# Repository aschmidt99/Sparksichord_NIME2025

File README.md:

# Sparksichord_NIME2025
 A repo for schematics, CAD, and audiovisual examples to accompany the NIME 2025 Sparksichord conference paper by Adam Schmidt, Jeffrey Snyder, Gian Torrano Jacobs, Joseph Gascho, Joyce Chen, and Andrew McPherson.

 Primary contact: a.schmidt24@imperial.ac.uk

The Sparksichord is a practical implementation of a 4-octave/48-channel Lorentz Force feedback sustainer system using brass strings, permanent magnets, optical sensors, and custom analog electronics. The Sparksichord is an augmentation of a 1970’s Zuckermann ‘Z-Box’ Harpsichord and uses its own keyboard to control the volume of each string’s feedback/actuation. Here we provide a basic overview of the working principles of the Sparksichord. For a more comprehensive guide to Lorentz Force actuation, please see _The Sparksichord: Practical Implementation of a Lorentz Force Electromagnetic Actuation and Feedback System_.

## Audiovisual example:

# Lorentz Force
The cumulative force felt by a charged particle exposed to electric and magnetic fields is known as the _Lorentz Force_. A special case of the Lorentz Force (sometimes referred to as the _Laplace Force_) describes the magnetic force felt by a current-carrying wire exposed to a magnetic field:

$$
\begin{align}
 \mathbf{F} = I \mathbf{L} \times \mathbf{B}
\end{align}
$$

where $\mathbf{F}$ is the force vector felt by the wire, $I$ is the current through the wire, $\mathbf{B}$ is the magnetic field vector, and $\mathbf{L}$ is the length of the wire exposed to the magnetic field.

Inputing an audio signal to the string such as white noise, you should hear the string vibrate most prominently at its natural resonant frequencies. It is possible to drive a string with an oscillator tuned to match the string’s fundamental frequency, but doing so can be tricky. Depending on the material properties of the actuated string, some of the actuation current may be dissipated as heat in the string’s internal resistance, introducing thermal expansion of the string and causing it to lengthen and reduce its tension. This brings the frequency of the string down causing it to no longer match the frequency of the open-loop actuation signal.

## Heat Buildup \& String Detuning

The resistivity of some conductive metals are displayed in the figure below. Metals such as yellow and red brass are much less resistive than iron and steel, meaning they are more robust to string detuning, though it should be noted that heat treatment or work-hardening of the string material is also a factor, where annealed metal will typically have higher conductivity than a heat-treated metal. Heat-treating or other processes that increase the stength of a metal string are often required for strings to withstand the tensions typically found in musical instruments, so it is fair to assume any wire intended for stringing instruments will have slightly greater resistivity than in the figure below.

The intensity of detuning is proportional to its heat buildup and therefore proportional to the resistivity inherent to the string:

$$
\begin{align}
  Q = I^2Rt
\end{align}
$$

where $Q$ = heat buildup, $I$ = electric current, $R$ = resistance, and $t$ = time. Though this formula suggests that the string may heat up and continue to detune indefinitely as electric current is applied, there is an element of heat dissipation into the surrounding air and any other materials the string is in contact with.  In other words, for a real system, the detuning effect from heat buildup eventually finds equilibrium with the heat dissipation, stabilizing the tuning for a given electric current at a given room temperature.

# Lorentz Force Feedback via Optical Sensor
An optical sensor (in our case, the ITR20403) can be used to sense the string's position. If this signal is sent back into the string via a power amplifier, the string should begin to feedback.

On the Sparksichord, an array of 48 sensors was placed above the strings.

# Dynamic Control Via Amplitude Limitation
We can control the feedback volume by introducing a voltage-controlled limiter. On the Sparksichord, the limiter control signal can from the instrument's own keys (see next section), an onboard potentiometer, or an external control voltage source.

# Controlling Feedback with Keyboard
To capture how far each key is pressed (to set each limiter circuit's threshold value), we use an array of QRD1114 Optical sensors placed at the back of the keyboard:

# 12-Channel PCB
There are four of these 12-channel sustainer control boards on the Sparksichord:

# Magnet Placement
Running AC signal through a string doesn't make the string vibrate unless there is a magnetic field nearby. To create a relatively uniform magnetic field for all of the strings, we created a rail that holds 24 N52 Neodymium magnets in uniformly-spaced slots. The position of each magnet can be adjusted to find a desirable feedback timbre:

# Acknowledgements
This work was supported by a UKRI Frontier Research (Consolidator) grant (EP/X023478/1) “RUDIMENTS: Reflective Understanding of Digital Instruments as Musical Entanglements” and by the Royal Academy of Engineering under the Research Chairs and Senior Research Fellowships scheme.
Early development of this work was supported in part by the University of Michigan Organ Department, University of Michigan ArtsEngine Arts Integrative Interdisciplinary Research (AiiR) Grant, and the University of Michigan EXCEL Enterprise Grant.

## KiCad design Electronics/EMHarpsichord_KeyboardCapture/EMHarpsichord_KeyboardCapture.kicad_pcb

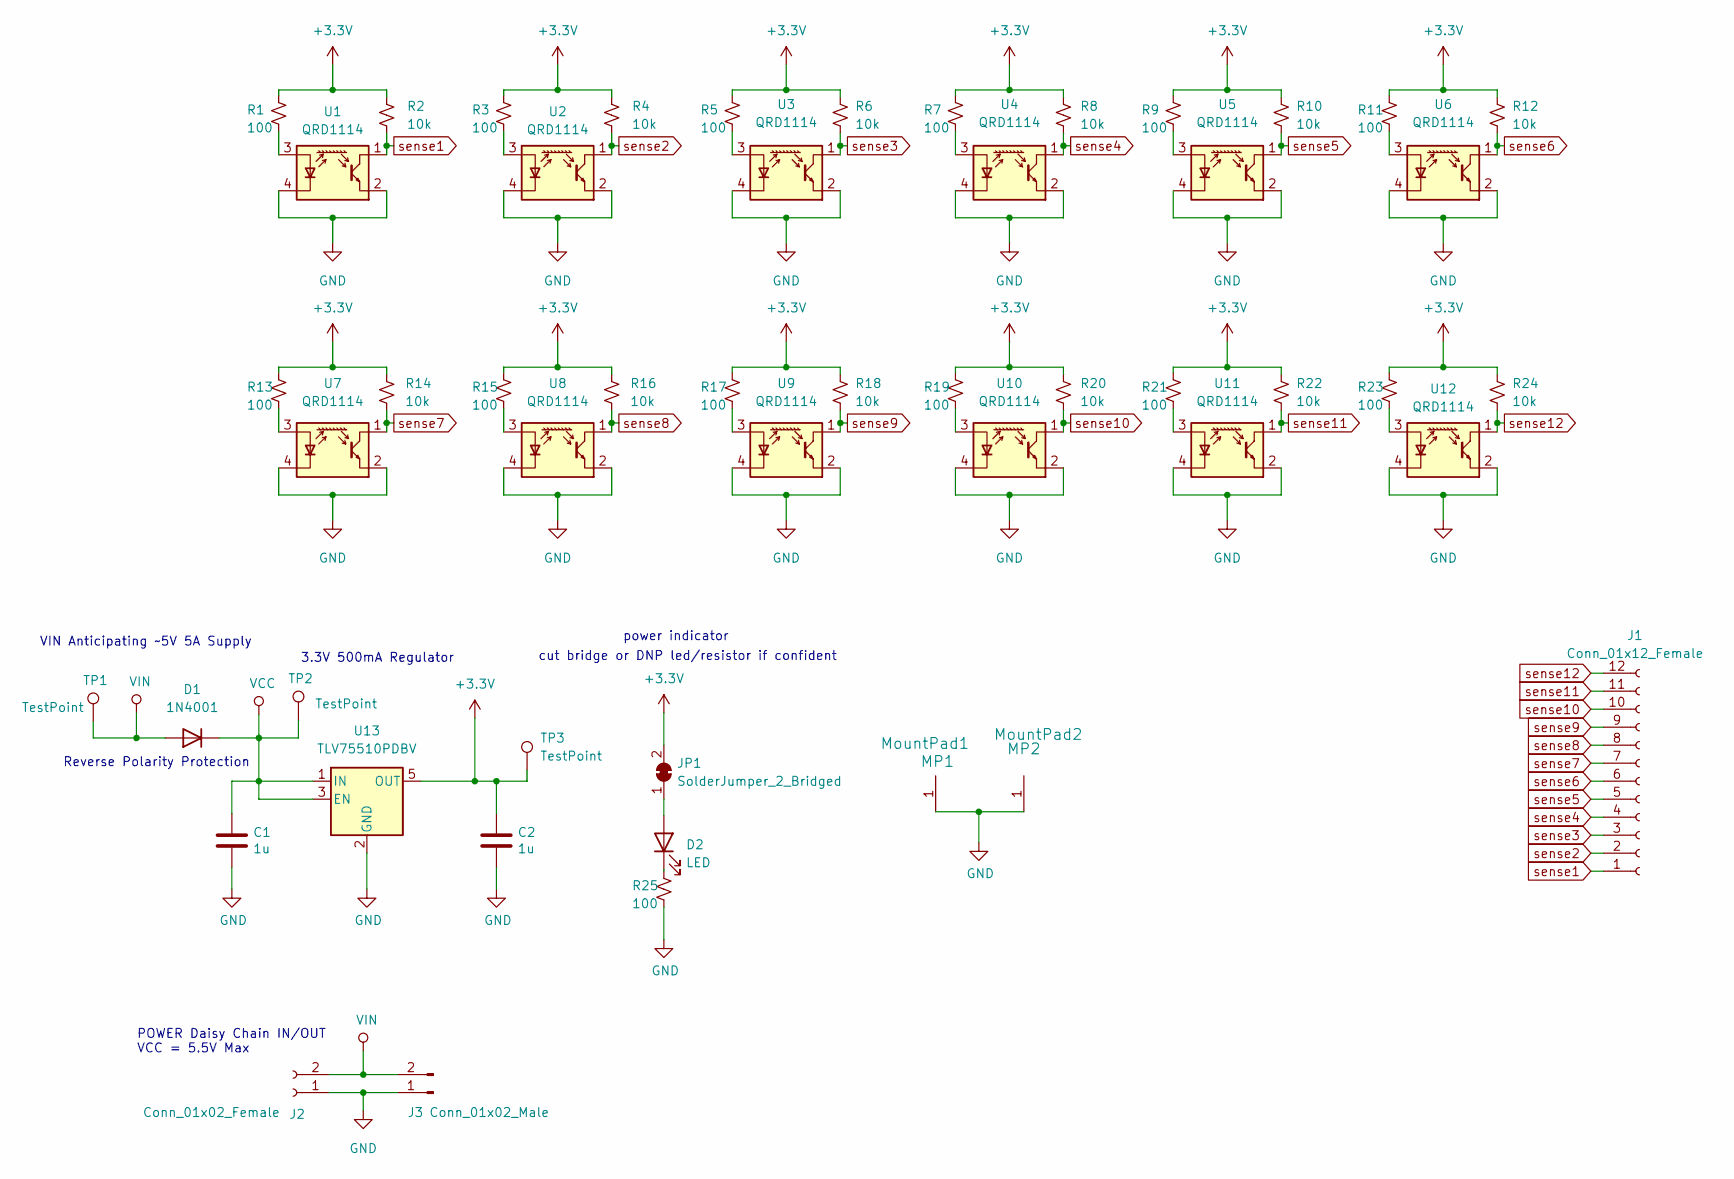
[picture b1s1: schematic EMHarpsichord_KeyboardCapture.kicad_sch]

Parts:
C1, C2: 1u; C_0603_1608Metric
D1: 1N4001; D_SOD-123
D2: LED; LED_0603_1608Metric
J1: Conn_01x12_Female; PinHeader_1x12_P2.54mm_Vertical
J2: Conn_01x02_Female; PinHeader_1x02_P2.54mm_Vertical
J3: Conn_01x02_Male; PinHeader_1x02_P2.54mm_Vertical
JP1: SolderJumper_2_Bridged; SolderJumper-2_P1.3mm_Bridged_RoundedPad1.0x1.5mm
MP1: MountPad1
MP2: MountPad2
R1, R3, R5, R7, R9, R11, R13, R15, R17, R19, R21, R23, R25: 100; R_0603_1608Metric
R2, R4, R6, R8, R10, R12, R14, R16, R18, R20, R22, R24: 10k; R_0603_1608Metric
TP1, TP2, TP3: TestPoint
U1, U2, U3, U4, U5, U6, U7, U8, U9, U10, U11, U12: QRD1114; OnSemi_QRD1114
U13: TLV75510PDBV; SOT-23-5

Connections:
+3.3V: C2.1, JP1.2 (B), R1.2, R2.2, R3.2, R4.2, R5.2, R6.2, R7.2, R8.2, R9.2, R10.2, R11.2, R12.2, R13.2, R14.2, R15.2, R16.2, R17.2, R18.2, R19.2, R20.2, R21.2, R22.2, R23.2, R24.2, TP3.1, U13.5 (OUT)
GND: C1.2, C2.2, J2.1, J3.1, MP1.1, MP2.1, R25.1, U1.2 (K), U1.4 (E), U2.2 (K), U2.4 (E), U3.2 (K), U3.4 (E), U4.2 (K), U4.4 (E), U5.2 (K), U5.4 (E), U6.2 (K), U6.4 (E), U7.2 (K), U7.4 (E), U8.2 (K), U8.4 (E), U9.2 (K), U9.4 (E), U10.2 (K), U10.4 (E), U11.2 (K), U11.4 (E), U12.2 (K), U12.4 (E), U13.2 (GND)
unnamed: D2.1 (K), R25.2
unnamed: D2.2 (A), JP1.1 (A)
unnamed: R1.1, U1.3 (C)
unnamed: R3.1, U2.3 (C)
unnamed: R5.1, U3.3 (C)
unnamed: R7.1, U4.3 (C)
unnamed: R9.1, U5.3 (C)
unnamed: R11.1, U6.3 (C)
unnamed: R13.1, U7.3 (C)
unnamed: R15.1, U8.3 (C)
unnamed: R17.1, U9.3 (C)
unnamed: R19.1, U10.3 (C)
unnamed: R21.1, U11.3 (C)
unnamed: R23.1, U12.3 (C)
VCC: C1.1, D1.1 (K), TP2.1, U13.1 (IN), U13.3 (EN)
VIN: D1.2 (A), J2.2, J3.2, TP1.1
sense1: J1.1, R2.1, U1.1 (A)
sense2: J1.2, R4.1, U2.1 (A)
sense3: J1.3, R6.1, U3.1 (A)
sense4: J1.4, R8.1, U4.1 (A)
sense5: J1.5, R10.1, U5.1 (A)
sense6: J1.6, R12.1, U6.1 (A)
sense7: J1.7, R14.1, U7.1 (A)
sense8: J1.8, R16.1, U8.1 (A)
sense9: J1.9, R18.1, U9.1 (A)
sense10: J1.10, R20.1, U10.1 (A)
sense11: J1.11, R22.1, U11.1 (A)
sense12: J1.12, R24.1, U12.1 (A)

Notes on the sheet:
3.3V 500mA Regulator
POWER Daisy Chain IN/OUT VCC = 5.5V Max
power indicator
Reverse Polarity Protection
VIN Anticipating ~5V 5A Supply
cut bridge or DNP led/resistor if confident

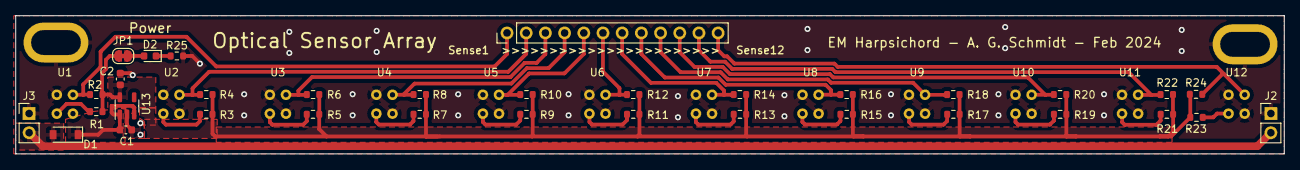
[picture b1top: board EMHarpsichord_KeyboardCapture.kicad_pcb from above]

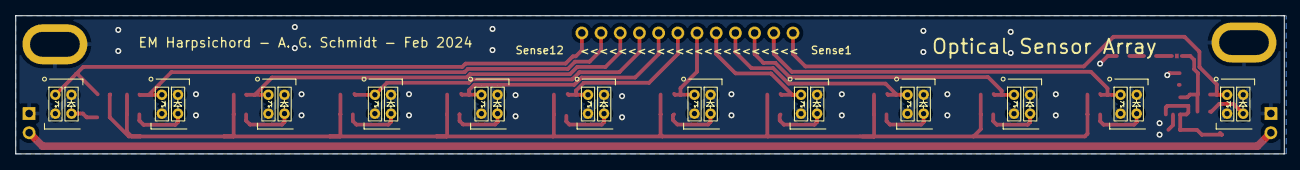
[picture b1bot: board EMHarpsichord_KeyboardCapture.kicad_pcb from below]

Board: 2 copper layers, 167.9 x 18.3 mm, 48 parts (12 on the bottom side), 30 nets.

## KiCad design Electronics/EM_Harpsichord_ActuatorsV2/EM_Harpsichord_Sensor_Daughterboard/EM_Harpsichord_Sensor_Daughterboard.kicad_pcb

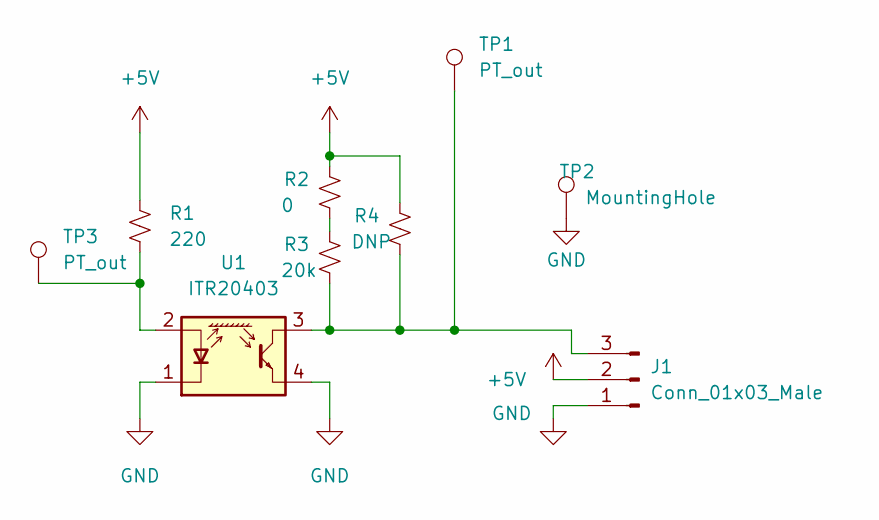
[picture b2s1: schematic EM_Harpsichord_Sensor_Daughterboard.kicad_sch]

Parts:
J1: Conn_01x03_Male; JST_XH_S3B-XH-A_1x03_P2.50mm_Horizontal; LCSC C161870
R1: 220; R_0603_1608Metric
R2: 0; R_0603_1608Metric
R3: 20k; R_0603_1608Metric
R4: DNP; R_0603_1608Metric
TP1, TP3: PT_out; TestPoint_THTPad_D2.0mm_Drill1.0mm
TP2: MountingHole; TestPoint_THTPad_D2.0mm_Drill1.0mm
U1: ITR20403; Everlight_ITR20403; LCSC C5135

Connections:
+5V: J1.2, R1.1, R2.1, R4.1
GND: J1.1, TP2.1, U1.1 (K), U1.4 (E)
unnamed: J1.3, R3.2, R4.2, TP1.1, U1.3 (C)
unnamed: R1.2, TP3.1, U1.2 (A)
unnamed: R2.2, R3.1

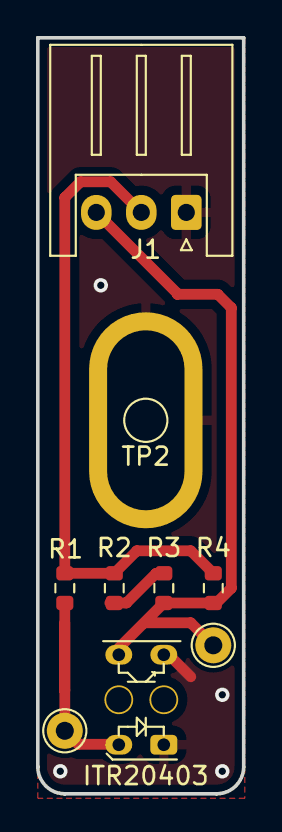
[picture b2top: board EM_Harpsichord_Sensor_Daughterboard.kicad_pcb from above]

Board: 2 copper layers, 11.4 x 42.0 mm, 9 parts (0 on the bottom side), 5 nets.

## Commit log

2025-04-20 Initial Commit
    Plenty of sorting to do. Initial commit before I accidentally delete/move something I didn't mean to
2025-04-20 Cleaning up
    cleaning up
2025-04-20 adding figures 1
2025-04-20 adding figures
2025-04-20 updating README
2025-04-20 adding youtube link
2025-04-20 readme
2025-04-20 readmen
